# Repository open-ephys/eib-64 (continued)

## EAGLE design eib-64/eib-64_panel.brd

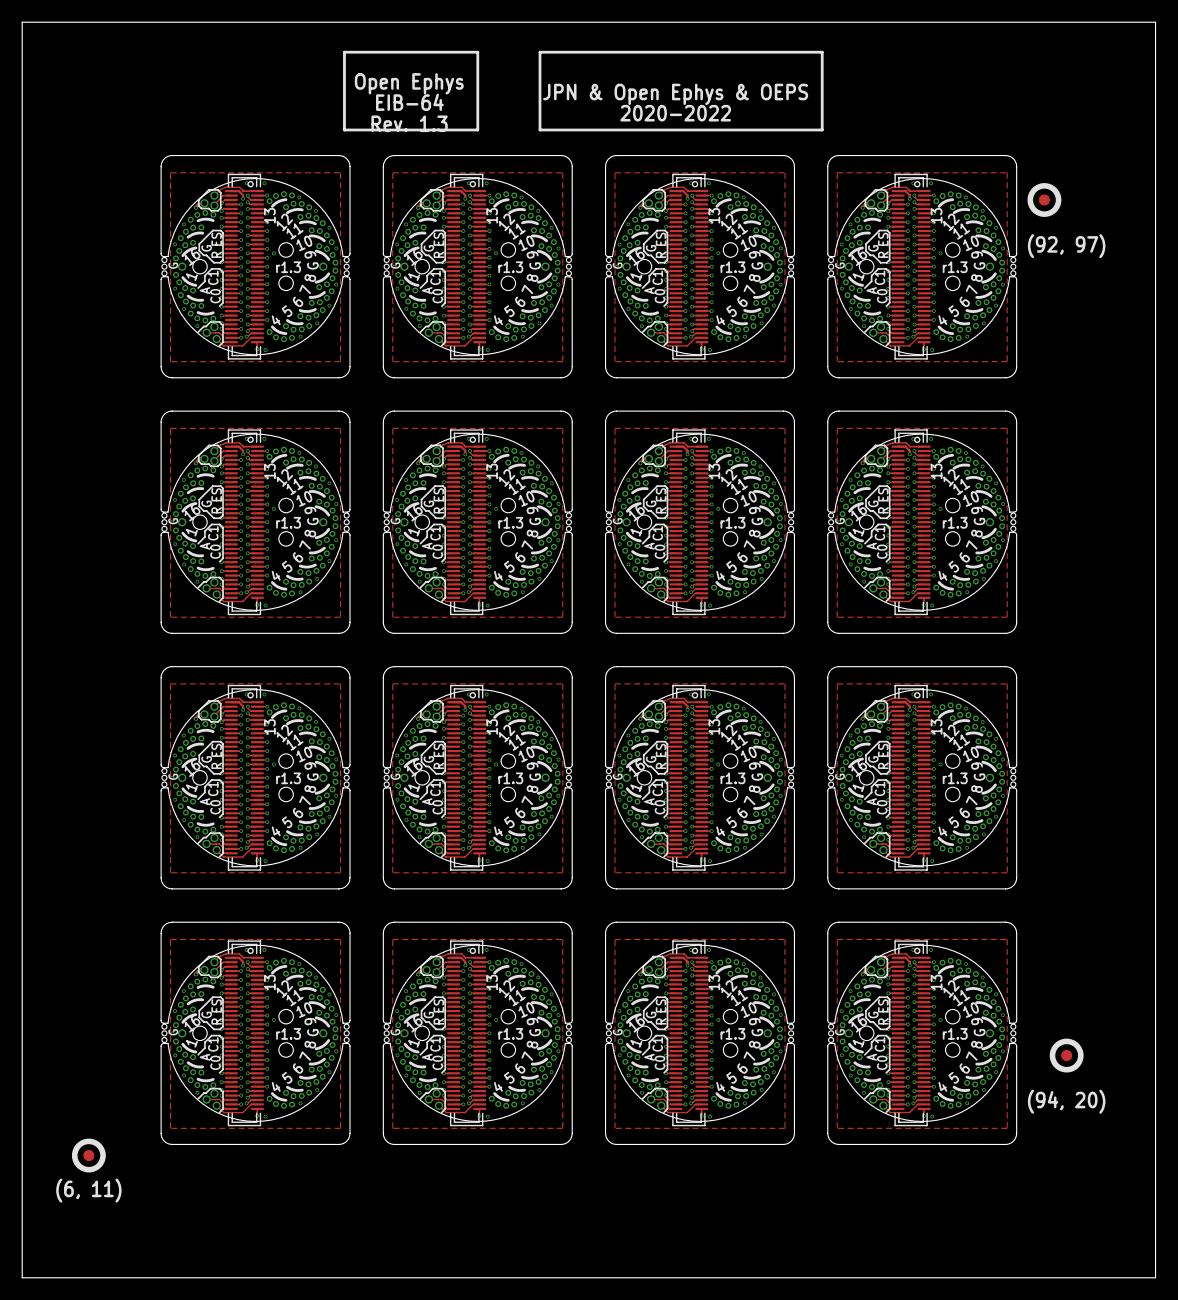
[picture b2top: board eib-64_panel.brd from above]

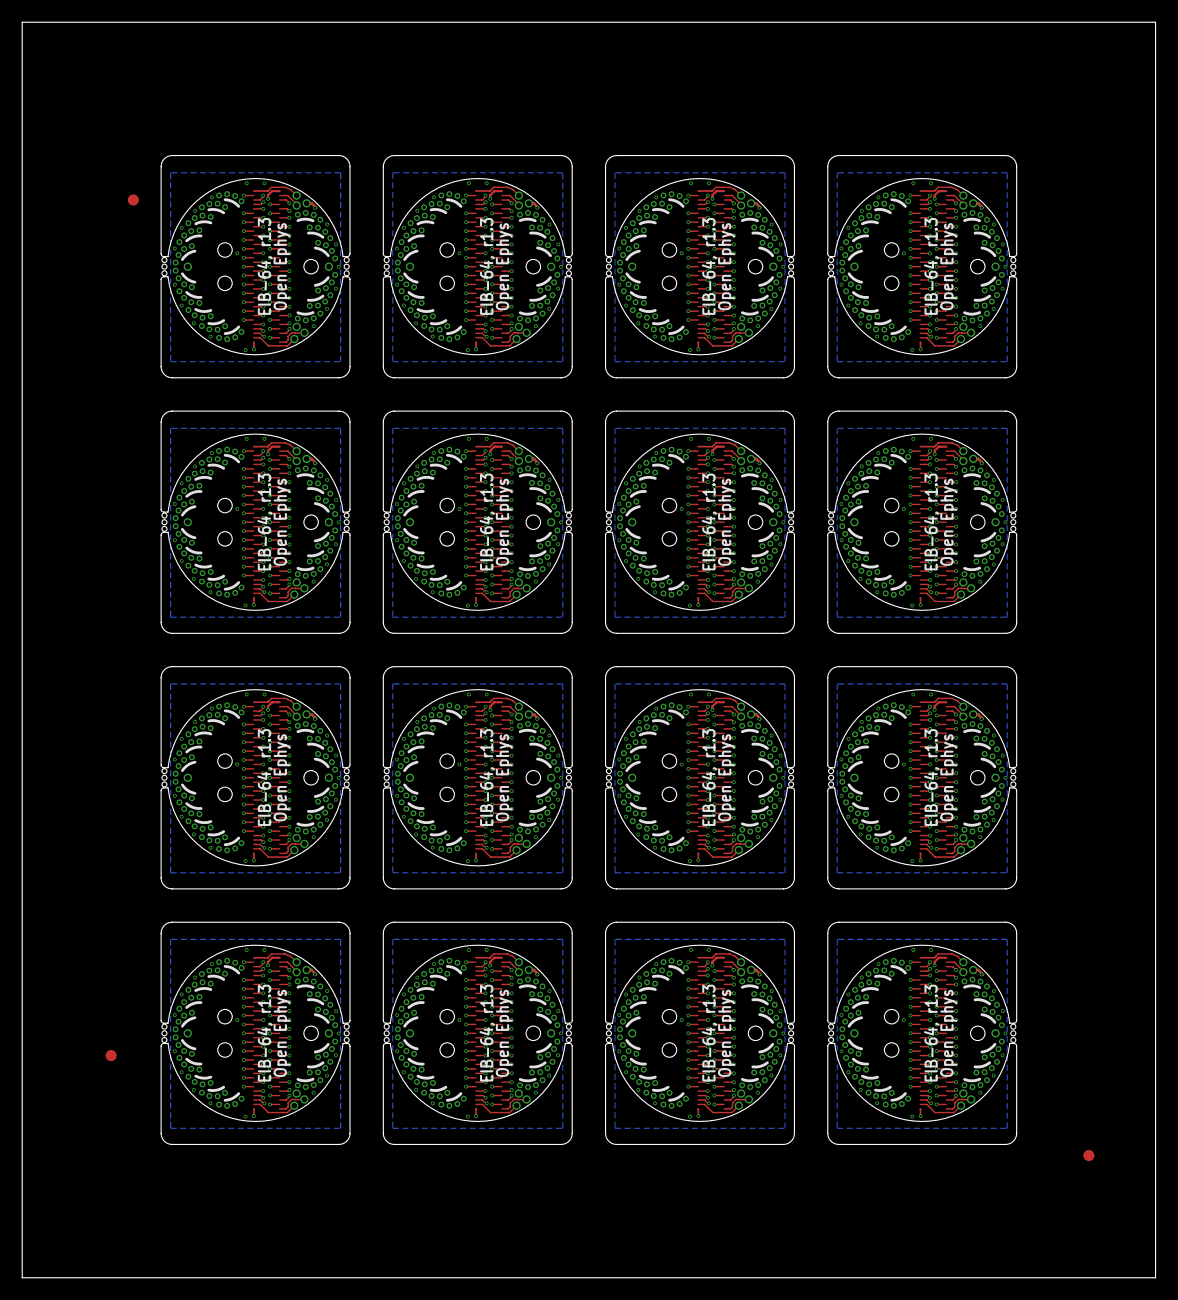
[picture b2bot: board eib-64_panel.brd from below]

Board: 4 copper layers, 102.0 x 113.0 mm, 403 parts (128 on the bottom side), 1120 nets.

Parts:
AN, AN1, AN2, AN3, AN4, AN5, AN6, AN7, AN8, AN9, AN10, AN11, AN12, AN13, AN14, AN15: LRG_GP; GOLDPIN_0.5ID_0.7OD
CAT0, CAT1, CAT2, CAT3, CAT4, CAT5, CAT6, CAT7, CAT8, CAT9, CAT10, CAT11, CAT12, CAT13, CAT14, CAT15, CAT16, CAT17, CAT18, CAT19, CAT20, CAT21, CAT22, CAT23, CAT24, CAT25, CAT26, CAT27, CAT28, CAT29, CAT30, CAT31: LRG_GP; GOLDPIN_0.5ID_0.7OD
E$1, E$2, E$4: FIDUCIAL
ESTIM, ESTIM1, ESTIM2, ESTIM3, ESTIM4, ESTIM5, ESTIM6, ESTIM7, ESTIM8, ESTIM9, ESTIM10, ESTIM11, ESTIM12, ESTIM13, ESTIM14, ESTIM15: LRG_GP; GOLDPIN_0.5ID_0.7OD
GND0, GND1, GND2, GND3, GND4, GND5, GND6, GND7, GND8, GND9, GND10, GND11, GND12, GND13, GND14, GND15, GND16, GND17, GND18, GND19, GND20, GND21, GND22, GND23, GND24, GND25, GND26, GND27, GND28, GND29, GND30, GND31: LRG_GP; GOLDPIN_0.5ID_0.7OD
J1, J2, J3, J4, J5, J6, J7, J8, J9, J10, J11, J12, J13, J14, J15, J16: DF40-REC; DF40-70REC
REF, REF1, REF2, REF3, REF4, REF5, REF6, REF7, REF8, REF9, REF10, REF11, REF12, REF13, REF14, REF15: LRG_GP; GOLDPIN_0.5ID_0.7OD
SHLD_A, SHLD_A1, SHLD_A2, SHLD_A3, SHLD_A4, SHLD_A5, SHLD_A6, SHLD_A7, SHLD_A8, SHLD_A9, SHLD_A10, SHLD_A11, SHLD_A12, SHLD_A13, SHLD_A14, SHLD_A15: LRG_GP; GOLDPIN_0.5ID_0.7OD
TET0, TET16, TET32, TET48, TET64, TET80, TET96, TET112, TET128, TET144, TET160, TET176, TET192, TET208, TET224, TET240: 0; TETRODE_0.3ID_LINEAR_MOUSE
TET1, TET17, TET33, TET49, TET65, TET81, TET97, TET113, TET129, TET145, TET161, TET177, TET193, TET209, TET225, TET241: 1; TETRODE_0.3ID_LINEAR_MOUSE
TET2, TET18, TET34, TET50, TET66, TET82, TET98, TET114, TET130, TET146, TET162, TET178, TET194, TET210, TET226, TET242: 2; TETRODE_0.3ID_LINEAR_MOUSE
TET3, TET19, TET35, TET51, TET67, TET83, TET99, TET115, TET131, TET147, TET163, TET179, TET195, TET211, TET227, TET243: 3; TETRODE_0.3ID_LINEAR_MOUSE
TET4, TET20, TET36, TET52, TET68, TET84, TET100, TET116, TET132, TET148, TET164, TET180, TET196, TET212, TET228, TET244: 4; TETRODE_0.3ID_LINEAR_MOUSE
TET5, TET21, TET37, TET53, TET69, TET85, TET101, TET117, TET133, TET149, TET165, TET181, TET197, TET213, TET229, TET245: 5; TETRODE_0.3ID_LINEAR_MOUSE
TET6, TET22, TET38, TET54, TET70, TET86, TET102, TET118, TET134, TET150, TET166, TET182, TET198, TET214, TET230, TET246: 6; TETRODE_0.3ID_LINEAR_MOUSE
TET7, TET23, TET39, TET55, TET71, TET87, TET103, TET119, TET135, TET151, TET167, TET183, TET199, TET215, TET231, TET247: 7; TETRODE_0.3ID_LINEAR_MOUSE
TET8, TET31, TET47, TET63, TET79, TET95, TET111, TET127, TET143, TET159, TET175, TET191, TET207, TET223, TET239, TET255: 8; TETRODE_0.3ID_LINEAR_MOUSE
TET9, TET30, TET46, TET62, TET78, TET94, TET110, TET126, TET142, TET158, TET174, TET190, TET206, TET222, TET238, TET254: 9; TETRODE_0.3ID_LINEAR_MOUSE
TET10, TET29, TET45, TET61, TET77, TET93, TET109, TET125, TET141, TET157, TET173, TET189, TET205, TET221, TET237, TET253: 10; TETRODE_0.3ID_LINEAR_MOUSE
TET11, TET28, TET44, TET60, TET76, TET92, TET108, TET124, TET140, TET156, TET172, TET188, TET204, TET220, TET236, TET252: 11; TETRODE_0.3ID_LINEAR_MOUSE
TET12, TET27, TET43, TET59, TET75, TET91, TET107, TET123, TET139, TET155, TET171, TET187, TET203, TET219, TET235, TET251: 12; TETRODE_0.3ID_LINEAR_MOUSE
TET13, TET26, TET42, TET58, TET74, TET90, TET106, TET122, TET138, TET154, TET170, TET186, TET202, TET218, TET234, TET250: 13; TETRODE_0.3ID_LINEAR_MOUSE
TET14, TET25, TET41, TET57, TET73, TET89, TET105, TET121, TET137, TET153, TET169, TET185, TET201, TET217, TET233, TET249: 14; TETRODE_0.3ID_LINEAR_MOUSE
TET15, TET24, TET40, TET56, TET72, TET88, TET104, TET120, TET136, TET152, TET168, TET184, TET200, TET216, TET232, TET248: 15; TETRODE_0.3ID_LINEAR_MOUSE

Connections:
AN: AN.P$1, J1.36
AN1: AN1.P$1, J2.36
AN2: AN2.P$1, J3.36
AN3: AN3.P$1, J4.36
AN4: AN4.P$1, J5.36
AN5: AN5.P$1, J6.36
AN6: AN6.P$1, J7.36
AN7: AN7.P$1, J8.36
AN8: AN8.P$1, J9.36
AN9: AN9.P$1, J10.36
AN10: AN10.P$1, J11.36
AN11: AN11.P$1, J12.36
AN12: AN12.P$1, J13.36
AN13: AN13.P$1, J14.36
AN14: AN14.P$1, J15.36
AN15: AN15.P$1, J16.36
CAT0: CAT0.P$1, J1.34
CAT1: CAT1.P$1, J1.35
CAT2: CAT2.P$1, J2.34
CAT3: CAT3.P$1, J2.35
CAT4: CAT4.P$1, J3.34
CAT5: CAT5.P$1, J3.35
CAT6: CAT6.P$1, J4.34
CAT7: CAT7.P$1, J4.35
CAT8: CAT8.P$1, J5.34
CAT9: CAT9.P$1, J5.35
CAT10: CAT10.P$1, J6.34
CAT11: CAT11.P$1, J6.35
CAT12: CAT12.P$1, J7.34
CAT13: CAT13.P$1, J7.35
CAT14: CAT14.P$1, J8.34
CAT15: CAT15.P$1, J8.35
CAT16: CAT16.P$1, J9.34
CAT17: CAT17.P$1, J9.35
CAT18: CAT18.P$1, J10.34
CAT19: CAT19.P$1, J10.35
CAT20: CAT20.P$1, J11.34
CAT21: CAT21.P$1, J11.35
CAT22: CAT22.P$1, J12.34
CAT23: CAT23.P$1, J12.35
CAT24: CAT24.P$1, J13.34
CAT25: CAT25.P$1, J13.35
CAT26: CAT26.P$1, J14.34
CAT27: CAT27.P$1, J14.35
CAT28: CAT28.P$1, J15.34
CAT29: CAT29.P$1, J15.35
CAT30: CAT30.P$1, J16.34
CAT31: CAT31.P$1, J16.35
ESTIM: ESTIM.P$1, J1.1
ESTIM1: ESTIM1.P$1, J2.1
ESTIM2: ESTIM2.P$1, J3.1
ESTIM3: ESTIM3.P$1, J4.1
ESTIM4: ESTIM4.P$1, J5.1
ESTIM5: ESTIM5.P$1, J6.1
ESTIM6: ESTIM6.P$1, J7.1
ESTIM7: ESTIM7.P$1, J8.1
ESTIM8: ESTIM8.P$1, J9.1
ESTIM9: ESTIM9.P$1, J10.1
ESTIM10: ESTIM10.P$1, J11.1
ESTIM11: ESTIM11.P$1, J12.1
ESTIM12: ESTIM12.P$1, J13.1
ESTIM13: ESTIM13.P$1, J14.1
ESTIM14: ESTIM14.P$1, J15.1
ESTIM15: ESTIM15.P$1, J16.1
GND: GND0.P$1, GND1.P$1, J1.70, SHLD_A.P$1
GND1: GND2.P$1, GND3.P$1, J2.70, SHLD_A1.P$1
GND2: GND4.P$1, GND5.P$1, J3.70, SHLD_A2.P$1
GND3: GND6.P$1, GND7.P$1, J4.70, SHLD_A3.P$1
GND4: GND8.P$1, GND9.P$1, J5.70, SHLD_A4.P$1
GND5: GND10.P$1, GND11.P$1, J6.70, SHLD_A5.P$1
GND6: GND12.P$1, GND13.P$1, J7.70, SHLD_A6.P$1
GND7: GND14.P$1, GND15.P$1, J8.70, SHLD_A7.P$1
GND8: GND16.P$1, GND17.P$1, J9.70, SHLD_A8.P$1
GND9: GND18.P$1, GND19.P$1, J10.70, SHLD_A9.P$1
GND10: GND20.P$1, GND21.P$1, J11.70, SHLD_A10.P$1
GND11: GND22.P$1, GND23.P$1, J12.70, SHLD_A11.P$1
GND12: GND24.P$1, GND25.P$1, J13.70, SHLD_A12.P$1
GND13: GND26.P$1, GND27.P$1, J14.70, SHLD_A13.P$1
GND14: GND28.P$1, GND29.P$1, J15.70, SHLD_A14.P$1
GND15: GND30.P$1, GND31.P$1, J16.70, SHLD_A15.P$1
unnamed: J1.68, TET12.3
unnamed: J1.65, TET12.2
unnamed: J1.66, TET12.1
unnamed: J1.67, TET12.0
unnamed: J1.64, TET13.0
unnamed: J1.63, TET13.1
unnamed: J1.62, TET13.2
unnamed: J1.61, TET13.3
unnamed: J1.60, TET14.0
unnamed: J1.59, TET14.1
unnamed: J1.58, TET14.2
unnamed: J1.57, TET14.3
unnamed: J1.56, TET15.0
unnamed: J1.55, TET15.1
unnamed: J1.54, TET15.2
unnamed: J1.53, TET15.3
unnamed: J1.52, TET0.3
unnamed: J1.51, TET0.2
unnamed: J1.50, TET0.1
unnamed: J1.49, TET0.0
unnamed: J1.48, TET1.3
unnamed: J1.47, TET1.2
unnamed: J1.46, TET1.1
unnamed: J1.45, TET1.0
unnamed: J1.44, TET2.3
unnamed: J1.43, TET2.2
unnamed: J1.42, TET2.1
unnamed: J1.41, TET2.0
unnamed: J1.40, TET3.0
unnamed: J1.39, TET3.3
unnamed: J1.38, TET3.2
unnamed: J1.37, TET3.1
unnamed: J1.5, TET11.3
unnamed: J1.4, TET11.2
unnamed: J1.3, TET11.1
unnamed: J1.2, TET11.0
unnamed: J2.33, TET20.0
unnamed: J2.32, TET20.1
unnamed: J2.31, TET20.2
unnamed: J2.30, TET20.3
unnamed: J2.29, TET21.0
unnamed: J2.28, TET21.1
unnamed: J2.27, TET21.2
unnamed: J2.26, TET21.3
unnamed: J2.25, TET22.0
unnamed: J2.24, TET22.1
unnamed: J2.23, TET22.2
unnamed: J2.22, TET22.3
unnamed: J2.21, TET23.0
unnamed: J2.20, TET23.1
unnamed: J2.19, TET23.2
unnamed: J2.18, TET23.3
unnamed: J2.17, TET31.3
unnamed: J2.16, TET31.2
unnamed: J2.15, TET31.1
unnamed: J2.14, TET31.0
unnamed: J2.13, TET30.3
unnamed: J2.12, TET30.2
unnamed: J2.11, TET30.1
unnamed: J2.10, TET30.0
unnamed: J2.9, TET29.3
unnamed: J2.8, TET29.2
unnamed: J2.7, TET29.1
unnamed: J2.6, TET29.0
unnamed: J2.68, TET27.3
unnamed: J2.66, TET27.1
unnamed: J2.64, TET26.0
unnamed: J2.63, TET26.1
unnamed: J2.62, TET26.2
unnamed: J2.61, TET26.3
unnamed: J2.60, TET25.0
unnamed: J2.59, TET25.1
unnamed: J2.58, TET25.2
unnamed: J2.57, TET25.3
unnamed: J2.56, TET24.0
unnamed: J2.55, TET24.1
unnamed: J2.54, TET24.2
unnamed: J2.53, TET24.3
unnamed: J2.52, TET16.3
unnamed: J2.51, TET16.2
unnamed: J2.50, TET16.1
unnamed: J2.49, TET16.0
unnamed: J2.48, TET17.3
unnamed: J2.47, TET17.2
unnamed: J2.46, TET17.1
unnamed: J2.45, TET17.0
unnamed: J2.44, TET18.3
unnamed: J2.43, TET18.2
unnamed: J2.42, TET18.1
unnamed: J2.41, TET18.0
unnamed: J2.40, TET19.0
unnamed: J2.38, TET19.2
unnamed: J2.5, TET28.3
unnamed: J2.4, TET28.2
unnamed: J2.3, TET28.1
unnamed: J2.2, TET28.0
unnamed: J2.65, TET27.2
unnamed: J2.67, TET27.0
unnamed: J2.39, TET19.3
unnamed: J2.37, TET19.1
unnamed: J3.33, TET36.0
unnamed: J3.32, TET36.1
unnamed: J3.31, TET36.2
unnamed: J3.30, TET36.3
unnamed: J3.29, TET37.0
unnamed: J3.28, TET37.1
unnamed: J3.27, TET37.2
unnamed: J3.26, TET37.3
unnamed: J3.25, TET38.0
unnamed: J3.24, TET38.1
unnamed: J3.23, TET38.2
unnamed: J3.22, TET38.3
unnamed: J3.21, TET39.0
unnamed: J3.20, TET39.1
unnamed: J3.19, TET39.2
unnamed: J3.18, TET39.3
unnamed: J3.17, TET47.3
unnamed: J3.16, TET47.2
unnamed: J3.15, TET47.1
unnamed: J3.14, TET47.0
unnamed: J3.13, TET46.3
unnamed: J3.12, TET46.2
unnamed: J3.11, TET46.1
unnamed: J3.10, TET46.0
unnamed: J3.9, TET45.3
unnamed: J3.8, TET45.2
unnamed: J3.7, TET45.1
unnamed: J3.6, TET45.0
unnamed: J3.68, TET43.3
unnamed: J3.66, TET43.1
unnamed: J3.64, TET42.0
unnamed: J3.63, TET42.1
unnamed: J3.62, TET42.2
unnamed: J3.61, TET42.3
unnamed: J3.60, TET41.0
unnamed: J3.59, TET41.1
unnamed: J3.58, TET41.2
unnamed: J3.57, TET41.3
unnamed: J3.56, TET40.0
unnamed: J3.55, TET40.1
unnamed: J3.54, TET40.2
unnamed: J3.53, TET40.3
unnamed: J3.52, TET32.3
unnamed: J3.51, TET32.2
unnamed: J3.50, TET32.1
unnamed: J3.49, TET32.0
unnamed: J3.48, TET33.3
unnamed: J3.47, TET33.2
unnamed: J3.46, TET33.1
unnamed: J3.45, TET33.0
unnamed: J3.44, TET34.3
unnamed: J3.43, TET34.2
unnamed: J3.42, TET34.1
unnamed: J3.41, TET34.0
unnamed: J3.40, TET35.0
unnamed: J3.38, TET35.2
unnamed: J3.5, TET44.3
unnamed: J3.4, TET44.2
unnamed: J3.3, TET44.1
unnamed: J3.2, TET44.0
unnamed: J3.65, TET43.2
unnamed: J3.67, TET43.0
unnamed: J3.39, TET35.3
unnamed: J3.37, TET35.1
unnamed: J4.33, TET52.0
unnamed: J4.32, TET52.1
unnamed: J4.31, TET52.2
unnamed: J4.30, TET52.3
unnamed: J4.29, TET53.0
unnamed: J4.28, TET53.1
unnamed: J4.27, TET53.2
unnamed: J4.26, TET53.3
unnamed: J4.25, TET54.0
unnamed: J4.24, TET54.1
unnamed: J4.23, TET54.2
unnamed: J4.22, TET54.3
unnamed: J4.21, TET55.0
unnamed: J4.20, TET55.1
unnamed: J4.19, TET55.2
unnamed: J4.18, TET55.3
unnamed: J4.17, TET63.3
unnamed: J4.16, TET63.2
unnamed: J4.15, TET63.1
unnamed: J4.14, TET63.0
unnamed: J4.13, TET62.3
unnamed: J4.12, TET62.2
unnamed: J4.11, TET62.1
unnamed: J4.10, TET62.0
unnamed: J4.9, TET61.3
unnamed: J4.8, TET61.2
unnamed: J4.7, TET61.1
unnamed: J4.6, TET61.0
unnamed: J4.68, TET59.3
unnamed: J4.66, TET59.1
unnamed: J4.64, TET58.0
unnamed: J4.63, TET58.1
unnamed: J4.62, TET58.2
unnamed: J4.61, TET58.3
unnamed: J1.33, TET4.0
unnamed: J1.32, TET4.1
unnamed: J1.31, TET4.2
unnamed: J1.30, TET4.3
unnamed: J1.29, TET5.0
unnamed: J1.28, TET5.1
unnamed: J1.27, TET5.2
unnamed: J1.26, TET5.3
unnamed: J1.25, TET6.0
unnamed: J1.24, TET6.1
unnamed: J1.23, TET6.2
unnamed: J1.22, TET6.3
unnamed: J1.21, TET7.0
unnamed: J1.20, TET7.1
unnamed: J1.19, TET7.2
unnamed: J1.18, TET7.3
unnamed: J1.17, TET8.3
unnamed: J1.16, TET8.2
unnamed: J1.15, TET8.1
unnamed: J1.14, TET8.0
unnamed: J1.13, TET9.3
unnamed: J1.12, TET9.2
unnamed: J1.11, TET9.1
unnamed: J1.10, TET9.0
unnamed: J1.9, TET10.3
unnamed: J1.8, TET10.2
unnamed: J1.7, TET10.1
unnamed: J1.6, TET10.0
unnamed: J4.60, TET57.0
unnamed: J4.59, TET57.1
unnamed: J4.58, TET57.2
unnamed: J4.57, TET57.3
unnamed: J4.56, TET56.0
unnamed: J4.55, TET56.1
unnamed: J4.54, TET56.2
unnamed: J4.53, TET56.3
unnamed: J4.52, TET48.3
unnamed: J4.51, TET48.2
unnamed: J4.50, TET48.1
unnamed: J4.49, TET48.0
unnamed: J4.48, TET49.3
unnamed: J4.47, TET49.2
unnamed: J4.46, TET49.1
unnamed: J4.45, TET49.0
unnamed: J4.44, TET50.3
unnamed: J4.43, TET50.2
unnamed: J4.42, TET50.1
unnamed: J4.41, TET50.0
unnamed: J4.40, TET51.0
unnamed: J4.38, TET51.2
unnamed: J4.5, TET60.3
unnamed: J4.4, TET60.2
unnamed: J4.3, TET60.1
unnamed: J4.2, TET60.0
unnamed: J4.65, TET59.2
unnamed: J4.67, TET59.0
unnamed: J4.39, TET51.3
unnamed: J4.37, TET51.1
unnamed: J5.33, TET68.0
unnamed: J5.32, TET68.1
unnamed: J5.31, TET68.2
unnamed: J5.30, TET68.3
unnamed: J5.29, TET69.0
unnamed: J5.28, TET69.1
unnamed: J5.27, TET69.2
unnamed: J5.26, TET69.3
unnamed: J5.25, TET70.0
unnamed: J5.24, TET70.1
unnamed: J5.23, TET70.2
unnamed: J5.22, TET70.3
unnamed: J5.21, TET71.0
unnamed: J5.20, TET71.1
unnamed: J5.19, TET71.2
unnamed: J5.18, TET71.3
unnamed: J5.17, TET79.3
unnamed: J5.16, TET79.2
unnamed: J5.15, TET79.1
unnamed: J5.14, TET79.0
unnamed: J5.13, TET78.3
unnamed: J5.12, TET78.2
unnamed: J5.11, TET78.1
unnamed: J5.10, TET78.0
unnamed: J5.9, TET77.3
unnamed: J5.8, TET77.2
unnamed: J5.7, TET77.1
unnamed: J5.6, TET77.0
unnamed: J5.68, TET75.3
unnamed: J5.66, TET75.1
unnamed: J5.64, TET74.0
unnamed: J5.63, TET74.1
unnamed: J5.62, TET74.2
unnamed: J5.61, TET74.3
unnamed: J5.60, TET73.0
unnamed: J5.59, TET73.1
unnamed: J5.58, TET73.2
unnamed: J5.57, TET73.3
unnamed: J5.56, TET72.0
unnamed: J5.55, TET72.1
unnamed: J5.54, TET72.2
unnamed: J5.53, TET72.3
unnamed: J5.52, TET64.3
unnamed: J5.51, TET64.2
unnamed: J5.50, TET64.1
unnamed: J5.49, TET64.0
unnamed: J5.48, TET65.3
unnamed: J5.47, TET65.2
unnamed: J5.46, TET65.1
unnamed: J5.45, TET65.0
unnamed: J5.44, TET66.3
unnamed: J5.43, TET66.2
unnamed: J5.42, TET66.1
unnamed: J5.41, TET66.0
unnamed: J5.40, TET67.0
unnamed: J5.38, TET67.2
unnamed: J5.5, TET76.3
unnamed: J5.4, TET76.2
unnamed: J5.3, TET76.1
unnamed: J5.2, TET76.0
unnamed: J5.65, TET75.2
unnamed: J5.67, TET75.0
unnamed: J5.39, TET67.3
unnamed: J5.37, TET67.1
unnamed: J6.33, TET84.0
unnamed: J6.32, TET84.1
unnamed: J6.31, TET84.2
unnamed: J6.30, TET84.3
unnamed: J6.29, TET85.0
unnamed: J6.28, TET85.1
unnamed: J6.27, TET85.2
unnamed: J6.26, TET85.3
unnamed: J6.25, TET86.0
unnamed: J6.24, TET86.1
unnamed: J6.23, TET86.2
unnamed: J6.22, TET86.3
unnamed: J6.21, TET87.0
unnamed: J6.20, TET87.1
unnamed: J6.19, TET87.2
unnamed: J6.18, TET87.3
unnamed: J6.17, TET95.3
unnamed: J6.16, TET95.2
unnamed: J6.15, TET95.1
unnamed: J6.14, TET95.0
unnamed: J6.13, TET94.3
unnamed: J6.12, TET94.2
unnamed: J6.11, TET94.1
unnamed: J6.10, TET94.0
unnamed: J6.9, TET93.3
unnamed: J6.8, TET93.2
unnamed: J6.7, TET93.1
unnamed: J6.6, TET93.0
unnamed: J6.68, TET91.3
unnamed: J6.66, TET91.1
unnamed: J6.64, TET90.0
unnamed: J6.63, TET90.1
unnamed: J6.62, TET90.2
unnamed: J6.61, TET90.3
unnamed: J6.60, TET89.0
unnamed: J6.59, TET89.1
unnamed: J6.58, TET89.2
unnamed: J6.57, TET89.3
unnamed: J6.56, TET88.0
unnamed: J6.55, TET88.1
unnamed: J6.54, TET88.2
unnamed: J6.53, TET88.3
unnamed: J6.52, TET80.3
unnamed: J6.51, TET80.2
unnamed: J6.50, TET80.1
unnamed: J6.49, TET80.0
unnamed: J6.48, TET81.3
unnamed: J6.47, TET81.2
unnamed: J6.46, TET81.1
unnamed: J6.45, TET81.0
unnamed: J6.44, TET82.3
unnamed: J6.43, TET82.2
unnamed: J6.42, TET82.1
unnamed: J6.41, TET82.0
unnamed: J6.40, TET83.0
unnamed: J6.38, TET83.2
unnamed: J6.5, TET92.3
unnamed: J6.4, TET92.2
unnamed: J6.3, TET92.1
unnamed: J6.2, TET92.0
unnamed: J6.65, TET91.2
unnamed: J6.67, TET91.0
unnamed: J6.39, TET83.3
unnamed: J6.37, TET83.1
unnamed: J7.33, TET100.0
unnamed: J7.32, TET100.1
unnamed: J7.31, TET100.2
unnamed: J7.30, TET100.3
unnamed: J7.29, TET101.0
unnamed: J7.28, TET101.1
unnamed: J7.27, TET101.2
unnamed: J7.26, TET101.3
unnamed: J7.25, TET102.0
unnamed: J7.24, TET102.1
unnamed: J7.23, TET102.2
unnamed: J7.22, TET102.3
unnamed: J7.21, TET103.0
unnamed: J7.20, TET103.1
unnamed: J7.19, TET103.2
unnamed: J7.18, TET103.3
unnamed: J7.17, TET111.3
unnamed: J7.16, TET111.2
unnamed: J7.15, TET111.1
unnamed: J7.14, TET111.0
unnamed: J7.13, TET110.3
unnamed: J7.12, TET110.2
unnamed: J7.11, TET110.1
unnamed: J7.10, TET110.0
unnamed: J7.9, TET109.3
unnamed: J7.8, TET109.2
unnamed: J7.7, TET109.1
unnamed: J7.6, TET109.0
unnamed: J7.68, TET107.3
unnamed: J7.66, TET107.1
unnamed: J7.64, TET106.0
unnamed: J7.63, TET106.1
unnamed: J7.62, TET106.2
unnamed: J7.61, TET106.3
unnamed: J7.60, TET105.0
unnamed: J7.59, TET105.1
unnamed: J7.58, TET105.2
unnamed: J7.57, TET105.3
unnamed: J7.56, TET104.0
unnamed: J7.55, TET104.1
unnamed: J7.54, TET104.2
unnamed: J7.53, TET104.3
unnamed: J7.52, TET96.3
unnamed: J7.51, TET96.2
unnamed: J7.50, TET96.1
unnamed: J7.49, TET96.0
unnamed: J7.48, TET97.3
unnamed: J7.47, TET97.2
unnamed: J7.46, TET97.1
unnamed: J7.45, TET97.0
unnamed: J7.44, TET98.3
unnamed: J7.43, TET98.2
unnamed: J7.42, TET98.1
unnamed: J7.41, TET98.0
unnamed: J7.40, TET99.0
unnamed: J7.38, TET99.2
unnamed: J7.5, TET108.3
unnamed: J7.4, TET108.2
unnamed: J7.3, TET108.1
unnamed: J7.2, TET108.0
unnamed: J7.65, TET107.2
unnamed: J7.67, TET107.0
unnamed: J7.39, TET99.3
unnamed: J7.37, TET99.1
unnamed: J8.33, TET116.0
unnamed: J8.32, TET116.1
unnamed: J8.31, TET116.2
unnamed: J8.30, TET116.3
unnamed: J8.29, TET117.0
unnamed: J8.28, TET117.1
unnamed: J8.27, TET117.2
unnamed: J8.26, TET117.3
unnamed: J8.25, TET118.0
unnamed: J8.24, TET118.1
unnamed: J8.23, TET118.2
unnamed: J8.22, TET118.3
unnamed: J8.21, TET119.0
unnamed: J8.20, TET119.1
unnamed: J8.19, TET119.2
unnamed: J8.18, TET119.3
unnamed: J8.17, TET127.3
unnamed: J8.16, TET127.2
unnamed: J8.15, TET127.1
unnamed: J8.14, TET127.0
unnamed: J8.13, TET126.3
unnamed: J8.12, TET126.2
unnamed: J8.11, TET126.1
unnamed: J8.10, TET126.0
unnamed: J8.9, TET125.3
unnamed: J8.8, TET125.2
unnamed: J8.7, TET125.1
unnamed: J8.6, TET125.0
unnamed: J8.68, TET123.3
unnamed: J8.66, TET123.1
unnamed: J8.64, TET122.0
unnamed: J8.63, TET122.1
unnamed: J8.62, TET122.2
unnamed: J8.61, TET122.3
unnamed: J8.60, TET121.0
unnamed: J8.59, TET121.1
unnamed: J8.58, TET121.2
unnamed: J8.57, TET121.3
unnamed: J8.56, TET120.0
unnamed: J8.55, TET120.1
unnamed: J8.54, TET120.2
unnamed: J8.53, TET120.3
unnamed: J8.52, TET112.3
unnamed: J8.51, TET112.2
unnamed: J8.50, TET112.1
unnamed: J8.49, TET112.0
unnamed: J8.48, TET113.3
unnamed: J8.47, TET113.2
unnamed: J8.46, TET113.1
unnamed: J8.45, TET113.0
unnamed: J8.44, TET114.3
unnamed: J8.43, TET114.2
unnamed: J8.42, TET114.1
unnamed: J8.41, TET114.0
unnamed: J8.40, TET115.0
unnamed: J8.38, TET115.2
unnamed: J8.5, TET124.3
unnamed: J8.4, TET124.2
unnamed: J8.3, TET124.1
unnamed: J8.2, TET124.0
unnamed: J8.65, TET123.2
unnamed: J8.67, TET123.0
unnamed: J8.39, TET115.3
unnamed: J8.37, TET115.1
unnamed: J9.33, TET132.0
unnamed: J9.32, TET132.1
unnamed: J9.31, TET132.2
unnamed: J9.30, TET132.3
unnamed: J9.29, TET133.0
unnamed: J9.28, TET133.1
unnamed: J9.27, TET133.2
unnamed: J9.26, TET133.3
unnamed: J9.25, TET134.0
unnamed: J9.24, TET134.1
unnamed: J9.23, TET134.2
unnamed: J9.22, TET134.3
unnamed: J9.21, TET135.0
unnamed: J9.20, TET135.1
unnamed: J9.19, TET135.2
unnamed: J9.18, TET135.3
unnamed: J9.17, TET143.3
unnamed: J9.16, TET143.2
unnamed: J9.15, TET143.1
unnamed: J9.14, TET143.0
unnamed: J9.13, TET142.3
unnamed: J9.12, TET142.2
unnamed: J9.11, TET142.1
unnamed: J9.10, TET142.0
unnamed: J9.9, TET141.3
unnamed: J9.8, TET141.2
unnamed: J9.7, TET141.1
unnamed: J9.6, TET141.0
unnamed: J9.68, TET139.3
unnamed: J9.66, TET139.1
unnamed: J9.64, TET138.0
unnamed: J9.63, TET138.1
unnamed: J9.62, TET138.2
unnamed: J9.61, TET138.3
unnamed: J9.60, TET137.0
unnamed: J9.59, TET137.1
unnamed: J9.58, TET137.2
unnamed: J9.57, TET137.3
unnamed: J9.56, TET136.0
unnamed: J9.55, TET136.1
unnamed: J9.54, TET136.2
unnamed: J9.53, TET136.3
unnamed: J9.52, TET128.3
unnamed: J9.51, TET128.2
unnamed: J9.50, TET128.1
unnamed: J9.49, TET128.0
unnamed: J9.48, TET129.3
unnamed: J9.47, TET129.2
unnamed: J9.46, TET129.1
unnamed: J9.45, TET129.0
unnamed: J9.44, TET130.3
unnamed: J9.43, TET130.2
unnamed: J9.42, TET130.1
unnamed: J9.41, TET130.0
unnamed: J9.40, TET131.0
unnamed: J9.38, TET131.2
unnamed: J9.5, TET140.3
unnamed: J9.4, TET140.2
unnamed: J9.3, TET140.1
unnamed: J9.2, TET140.0
unnamed: J9.65, TET139.2
unnamed: J9.67, TET139.0
unnamed: J9.39, TET131.3
unnamed: J9.37, TET131.1
unnamed: J10.33, TET148.0
unnamed: J10.32, TET148.1
unnamed: J10.31, TET148.2
unnamed: J10.30, TET148.3
unnamed: J10.29, TET149.0
unnamed: J10.28, TET149.1
unnamed: J10.27, TET149.2
unnamed: J10.26, TET149.3
unnamed: J10.25, TET150.0
unnamed: J10.24, TET150.1
unnamed: J10.23, TET150.2
unnamed: J10.22, TET150.3
unnamed: J10.21, TET151.0
unnamed: J10.20, TET151.1
unnamed: J10.19, TET151.2
unnamed: J10.18, TET151.3
unnamed: J10.17, TET159.3
unnamed: J10.16, TET159.2
unnamed: J10.15, TET159.1
unnamed: J10.14, TET159.0
unnamed: J10.13, TET158.3
unnamed: J10.12, TET158.2
unnamed: J10.11, TET158.1
unnamed: J10.10, TET158.0
unnamed: J10.9, TET157.3
unnamed: J10.8, TET157.2
unnamed: J10.7, TET157.1
unnamed: J10.6, TET157.0
unnamed: J10.68, TET155.3
unnamed: J10.66, TET155.1
unnamed: J10.64, TET154.0
unnamed: J10.63, TET154.1
unnamed: J10.62, TET154.2
unnamed: J10.61, TET154.3
unnamed: J10.60, TET153.0
unnamed: J10.59, TET153.1
unnamed: J10.58, TET153.2
unnamed: J10.57, TET153.3
unnamed: J10.56, TET152.0
unnamed: J10.55, TET152.1
unnamed: J10.54, TET152.2
unnamed: J10.53, TET152.3
unnamed: J10.52, TET144.3
unnamed: J10.51, TET144.2
unnamed: J10.50, TET144.1
unnamed: J10.49, TET144.0
unnamed: J10.48, TET145.3
unnamed: J10.47, TET145.2
unnamed: J10.46, TET145.1
unnamed: J10.45, TET145.0
unnamed: J10.44, TET146.3
unnamed: J10.43, TET146.2
unnamed: J10.42, TET146.1
unnamed: J10.41, TET146.0
unnamed: J10.40, TET147.0
unnamed: J10.38, TET147.2
unnamed: J10.5, TET156.3
unnamed: J10.4, TET156.2
unnamed: J10.3, TET156.1
unnamed: J10.2, TET156.0
unnamed: J10.65, TET155.2
unnamed: J10.67, TET155.0
unnamed: J10.39, TET147.3
unnamed: J10.37, TET147.1
unnamed: J11.33, TET164.0
unnamed: J11.32, TET164.1
unnamed: J11.31, TET164.2
unnamed: J11.30, TET164.3
unnamed: J11.29, TET165.0
unnamed: J11.28, TET165.1
unnamed: J11.27, TET165.2
unnamed: J11.26, TET165.3
unnamed: J11.25, TET166.0
unnamed: J11.24, TET166.1
unnamed: J11.23, TET166.2
unnamed: J11.22, TET166.3
unnamed: J11.21, TET167.0
unnamed: J11.20, TET167.1
unnamed: J11.19, TET167.2
unnamed: J11.18, TET167.3
unnamed: J11.17, TET175.3
unnamed: J11.16, TET175.2
unnamed: J11.15, TET175.1
unnamed: J11.14, TET175.0
unnamed: J11.13, TET174.3
unnamed: J11.12, TET174.2
unnamed: J11.11, TET174.1
unnamed: J11.10, TET174.0
unnamed: J11.9, TET173.3
unnamed: J11.8, TET173.2
unnamed: J11.7, TET173.1
unnamed: J11.6, TET173.0
unnamed: J11.68, TET171.3
unnamed: J11.66, TET171.1
unnamed: J11.64, TET170.0
unnamed: J11.63, TET170.1
unnamed: J11.62, TET170.2
unnamed: J11.61, TET170.3
unnamed: J11.60, TET169.0
unnamed: J11.59, TET169.1
unnamed: J11.58, TET169.2
unnamed: J11.57, TET169.3
unnamed: J11.56, TET168.0
unnamed: J11.55, TET168.1
unnamed: J11.54, TET168.2
unnamed: J11.53, TET168.3
unnamed: J11.52, TET160.3
unnamed: J11.51, TET160.2
unnamed: J11.50, TET160.1
unnamed: J11.49, TET160.0
unnamed: J11.48, TET161.3
unnamed: J11.47, TET161.2
unnamed: J11.46, TET161.1
unnamed: J11.45, TET161.0
unnamed: J11.44, TET162.3
unnamed: J11.43, TET162.2
unnamed: J11.42, TET162.1
unnamed: J11.41, TET162.0
unnamed: J11.40, TET163.0
unnamed: J11.38, TET163.2
unnamed: J11.5, TET172.3
unnamed: J11.4, TET172.2
unnamed: J11.3, TET172.1
unnamed: J11.2, TET172.0
unnamed: J11.65, TET171.2
unnamed: J11.67, TET171.0
unnamed: J11.39, TET163.3
unnamed: J11.37, TET163.1
unnamed: J12.33, TET180.0
unnamed: J12.32, TET180.1
unnamed: J12.31, TET180.2
unnamed: J12.30, TET180.3
unnamed: J12.29, TET181.0
unnamed: J12.28, TET181.1
unnamed: J12.27, TET181.2
unnamed: J12.26, TET181.3
unnamed: J12.25, TET182.0
unnamed: J12.24, TET182.1
unnamed: J12.23, TET182.2
unnamed: J12.22, TET182.3
unnamed: J12.21, TET183.0
unnamed: J12.20, TET183.1
unnamed: J12.19, TET183.2
unnamed: J12.18, TET183.3
unnamed: J12.17, TET191.3
unnamed: J12.16, TET191.2
unnamed: J12.15, TET191.1
unnamed: J12.14, TET191.0
unnamed: J12.13, TET190.3
unnamed: J12.12, TET190.2
unnamed: J12.11, TET190.1
unnamed: J12.10, TET190.0
unnamed: J12.9, TET189.3
unnamed: J12.8, TET189.2
unnamed: J12.7, TET189.1
unnamed: J12.6, TET189.0
unnamed: J12.68, TET187.3
unnamed: J12.66, TET187.1
unnamed: J12.64, TET186.0
unnamed: J12.63, TET186.1
unnamed: J12.62, TET186.2
unnamed: J12.61, TET186.3
unnamed: J12.60, TET185.0
unnamed: J12.59, TET185.1
unnamed: J12.58, TET185.2
unnamed: J12.57, TET185.3
unnamed: J12.56, TET184.0
unnamed: J12.55, TET184.1
unnamed: J12.54, TET184.2
unnamed: J12.53, TET184.3
unnamed: J12.52, TET176.3
unnamed: J12.51, TET176.2
unnamed: J12.50, TET176.1
unnamed: J12.49, TET176.0
unnamed: J12.48, TET177.3
unnamed: J12.47, TET177.2
unnamed: J12.46, TET177.1
unnamed: J12.45, TET177.0
unnamed: J12.44, TET178.3
unnamed: J12.43, TET178.2
unnamed: J12.42, TET178.1
unnamed: J12.41, TET178.0
unnamed: J12.40, TET179.0
unnamed: J12.38, TET179.2
unnamed: J12.5, TET188.3
unnamed: J12.4, TET188.2
unnamed: J12.3, TET188.1
unnamed: J12.2, TET188.0
unnamed: J12.65, TET187.2
unnamed: J12.67, TET187.0
unnamed: J12.39, TET179.3
unnamed: J12.37, TET179.1
unnamed: J13.33, TET196.0
unnamed: J13.32, TET196.1
unnamed: J13.31, TET196.2
unnamed: J13.30, TET196.3
unnamed: J13.29, TET197.0
unnamed: J13.28, TET197.1
unnamed: J13.27, TET197.2
unnamed: J13.26, TET197.3
unnamed: J13.25, TET198.0
unnamed: J13.24, TET198.1
unnamed: J13.23, TET198.2
unnamed: J13.22, TET198.3
unnamed: J13.21, TET199.0
unnamed: J13.20, TET199.1
unnamed: J13.19, TET199.2
unnamed: J13.18, TET199.3
unnamed: J13.17, TET207.3
unnamed: J13.16, TET207.2
unnamed: J13.15, TET207.1
unnamed: J13.14, TET207.0
unnamed: J13.13, TET206.3
unnamed: J13.12, TET206.2
unnamed: J13.11, TET206.1
unnamed: J13.10, TET206.0
unnamed: J13.9, TET205.3
unnamed: J13.8, TET205.2
unnamed: J13.7, TET205.1
unnamed: J13.6, TET205.0
unnamed: J13.68, TET203.3
unnamed: J13.66, TET203.1
unnamed: J13.64, TET202.0
unnamed: J13.63, TET202.1
unnamed: J13.62, TET202.2
unnamed: J13.61, TET202.3
unnamed: J13.60, TET201.0
unnamed: J13.59, TET201.1
unnamed: J13.58, TET201.2
unnamed: J13.57, TET201.3
unnamed: J13.56, TET200.0
unnamed: J13.55, TET200.1
unnamed: J13.54, TET200.2
unnamed: J13.53, TET200.3
unnamed: J13.52, TET192.3
unnamed: J13.51, TET192.2
unnamed: J13.50, TET192.1
unnamed: J13.49, TET192.0
unnamed: J13.48, TET193.3
unnamed: J13.47, TET193.2
unnamed: J13.46, TET193.1
unnamed: J13.45, TET193.0
unnamed: J13.44, TET194.3
unnamed: J13.43, TET194.2
unnamed: J13.42, TET194.1
unnamed: J13.41, TET194.0
unnamed: J13.40, TET195.0
unnamed: J13.38, TET195.2
unnamed: J13.5, TET204.3
unnamed: J13.4, TET204.2
unnamed: J13.3, TET204.1
unnamed: J13.2, TET204.0
unnamed: J13.65, TET203.2
unnamed: J13.67, TET203.0
unnamed: J13.39, TET195.3
unnamed: J13.37, TET195.1
unnamed: J14.33, TET212.0
unnamed: J14.32, TET212.1
unnamed: J14.31, TET212.2
unnamed: J14.30, TET212.3
unnamed: J14.29, TET213.0
unnamed: J14.28, TET213.1
unnamed: J14.27, TET213.2
unnamed: J14.26, TET213.3
unnamed: J14.25, TET214.0
unnamed: J14.24, TET214.1
unnamed: J14.23, TET214.2
unnamed: J14.22, TET214.3
unnamed: J14.21, TET215.0
unnamed: J14.20, TET215.1
unnamed: J14.19, TET215.2
unnamed: J14.18, TET215.3
unnamed: J14.17, TET223.3
unnamed: J14.16, TET223.2
unnamed: J14.15, TET223.1
unnamed: J14.14, TET223.0
unnamed: J14.13, TET222.3
unnamed: J14.12, TET222.2
unnamed: J14.11, TET222.1
unnamed: J14.10, TET222.0
unnamed: J14.9, TET221.3
unnamed: J14.8, TET221.2
unnamed: J14.7, TET221.1
unnamed: J14.6, TET221.0
unnamed: J14.68, TET219.3
unnamed: J14.66, TET219.1
unnamed: J14.64, TET218.0
unnamed: J14.63, TET218.1
unnamed: J14.62, TET218.2
unnamed: J14.61, TET218.3
unnamed: J14.60, TET217.0
unnamed: J14.59, TET217.1
unnamed: J14.58, TET217.2
unnamed: J14.57, TET217.3
unnamed: J14.56, TET216.0
unnamed: J14.55, TET216.1
unnamed: J14.54, TET216.2
unnamed: J14.53, TET216.3
unnamed: J14.52, TET208.3
unnamed: J14.51, TET208.2
unnamed: J14.50, TET208.1
unnamed: J14.49, TET208.0
unnamed: J14.48, TET209.3
unnamed: J14.47, TET209.2
unnamed: J14.46, TET209.1
unnamed: J14.45, TET209.0
unnamed: J14.44, TET210.3
unnamed: J14.43, TET210.2
unnamed: J14.42, TET210.1
unnamed: J14.41, TET210.0
unnamed: J14.40, TET211.0
unnamed: J14.38, TET211.2
unnamed: J14.5, TET220.3
unnamed: J14.4, TET220.2
unnamed: J14.3, TET220.1
unnamed: J14.2, TET220.0
unnamed: J14.65, TET219.2
unnamed: J14.67, TET219.0
unnamed: J14.39, TET211.3
unnamed: J14.37, TET211.1
unnamed: J15.33, TET228.0
unnamed: J15.32, TET228.1
unnamed: J15.31, TET228.2
unnamed: J15.30, TET228.3
unnamed: J15.29, TET229.0
unnamed: J15.28, TET229.1
unnamed: J15.27, TET229.2
unnamed: J15.26, TET229.3
unnamed: J15.25, TET230.0
unnamed: J15.24, TET230.1
unnamed: J15.23, TET230.2
unnamed: J15.22, TET230.3
unnamed: J15.21, TET231.0
unnamed: J15.20, TET231.1
unnamed: J15.19, TET231.2
unnamed: J15.18, TET231.3
unnamed: J15.17, TET239.3
unnamed: J15.16, TET239.2
unnamed: J15.15, TET239.1
unnamed: J15.14, TET239.0
unnamed: J15.13, TET238.3
unnamed: J15.12, TET238.2
unnamed: J15.11, TET238.1
unnamed: J15.10, TET238.0
unnamed: J15.9, TET237.3
unnamed: J15.8, TET237.2
unnamed: J15.7, TET237.1
unnamed: J15.6, TET237.0
unnamed: J15.68, TET235.3
unnamed: J15.66, TET235.1
unnamed: J15.64, TET234.0
unnamed: J15.63, TET234.1
unnamed: J15.62, TET234.2
unnamed: J15.61, TET234.3
unnamed: J15.60, TET233.0
unnamed: J15.59, TET233.1
unnamed: J15.58, TET233.2
unnamed: J15.57, TET233.3
unnamed: J15.56, TET232.0
unnamed: J15.55, TET232.1
unnamed: J15.54, TET232.2
unnamed: J15.53, TET232.3
unnamed: J15.52, TET224.3
unnamed: J15.51, TET224.2
unnamed: J15.50, TET224.1
unnamed: J15.49, TET224.0
unnamed: J15.48, TET225.3
unnamed: J15.47, TET225.2
unnamed: J15.46, TET225.1
unnamed: J15.45, TET225.0
unnamed: J15.44, TET226.3
unnamed: J15.43, TET226.2
unnamed: J15.42, TET226.1
unnamed: J15.41, TET226.0
unnamed: J15.40, TET227.0
unnamed: J15.38, TET227.2
unnamed: J15.5, TET236.3
unnamed: J15.4, TET236.2
unnamed: J15.3, TET236.1
unnamed: J15.2, TET236.0
unnamed: J15.65, TET235.2
unnamed: J15.67, TET235.0
unnamed: J15.39, TET227.3
unnamed: J15.37, TET227.1
unnamed: J16.33, TET244.0
unnamed: J16.32, TET244.1
unnamed: J16.31, TET244.2
unnamed: J16.30, TET244.3
unnamed: J16.29, TET245.0
unnamed: J16.28, TET245.1
unnamed: J16.27, TET245.2
unnamed: J16.26, TET245.3
unnamed: J16.25, TET246.0
unnamed: J16.24, TET246.1
unnamed: J16.23, TET246.2
unnamed: J16.22, TET246.3
unnamed: J16.21, TET247.0
unnamed: J16.20, TET247.1
unnamed: J16.19, TET247.2
unnamed: J16.18, TET247.3
unnamed: J16.17, TET255.3
unnamed: J16.16, TET255.2
unnamed: J16.15, TET255.1
unnamed: J16.14, TET255.0
unnamed: J16.13, TET254.3
unnamed: J16.12, TET254.2
unnamed: J16.11, TET254.1
unnamed: J16.10, TET254.0
unnamed: J16.9, TET253.3
unnamed: J16.8, TET253.2
unnamed: J16.7, TET253.1
unnamed: J16.6, TET253.0
unnamed: J16.68, TET251.3
unnamed: J16.66, TET251.1
unnamed: J16.64, TET250.0
unnamed: J16.63, TET250.1
unnamed: J16.62, TET250.2
unnamed: J16.61, TET250.3
unnamed: J16.60, TET249.0
unnamed: J16.59, TET249.1
unnamed: J16.58, TET249.2
unnamed: J16.57, TET249.3
unnamed: J16.56, TET248.0
unnamed: J16.55, TET248.1
unnamed: J16.54, TET248.2
unnamed: J16.53, TET248.3
unnamed: J16.52, TET240.3
unnamed: J16.51, TET240.2
unnamed: J16.50, TET240.1
unnamed: J16.49, TET240.0
unnamed: J16.48, TET241.3
unnamed: J16.47, TET241.2
unnamed: J16.46, TET241.1
unnamed: J16.45, TET241.0
unnamed: J16.44, TET242.3
unnamed: J16.43, TET242.2
unnamed: J16.42, TET242.1
unnamed: J16.41, TET242.0
unnamed: J16.40, TET243.0
unnamed: J16.38, TET243.2
unnamed: J16.5, TET252.3
unnamed: J16.4, TET252.2
unnamed: J16.3, TET252.1
unnamed: J16.2, TET252.0
unnamed: J16.65, TET251.2
unnamed: J16.67, TET251.0
unnamed: J16.39, TET243.3
unnamed: J16.37, TET243.1
REF: J1.69, REF.P$1
REF1: J2.69, REF1.P$1
REF2: J3.69, REF2.P$1
REF3: J4.69, REF3.P$1
REF4: J5.69, REF4.P$1
REF5: J6.69, REF5.P$1
REF6: J7.69, REF6.P$1
REF7: J8.69, REF7.P$1
REF8: J9.69, REF8.P$1
REF9: J10.69, REF9.P$1
REF10: J11.69, REF10.P$1
REF11: J12.69, REF11.P$1
REF12: J13.69, REF12.P$1
REF13: J14.69, REF13.P$1
REF14: J15.69, REF14.P$1
REF15: J16.69, REF15.P$1

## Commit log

2017-11-18 Created eib-64
    - Fits headstage-64
    - Also, put a keepout layer in eib-128 and eib-256 around the edge where
    the PCB makes contact with the drive body
2017-12-03 Fixed missing 1.8v power intput to serializer in headstage-64
    - Added values to components missing them
    - Completed ERC and DRC
    - Should be ready for fab pending final checks by other ppl
2017-12-23 Getting documentation and licensing in order
    - All subdirectories need to have their own README and license
    - This commit starts doing that
2017-12-24 More README updates
    - READMEs for the nanoz adapters
    - Links provided in top level README
2017-12-29 oepcie Specification.md update
    - Text before actual API is pretty much up to date with the latest
    firmware
    - Small changes to some READMEs
2018-03-12 Minor improvements to headstage-256 routing
    - Also remove all eagle.epf files because they are useless
2018-04-05 Reduced size of eib-64
    - Also created v-cut panelized board with 12 eibs
2018-04-15 Lots of small fixes and cleanup
    - Taking care of little issues that have been bothering me
    - Dediated serdes interface board moved to deprecated
    - Non-serialized headstage moved to deprecated
    - Deleted top-level datasheets directory which does not really
    apply to anything anymore
    - Added pdfs versions of board schematics so that eagle is not
2018-04-15 More cleanup
    - Add stencil gerbers for all eibs and eib panels
    - Remove unused intermediate design files
2018-04-19 Updated eib-64 to meet seeed low-cost spec
    - 8 mil trace/pour spacing
    - Added stencil gerbers as well
2018-08-27 eib-64 rev. 1.1
    - Fits latest shuttle drive reatining feature.
2018-10-14 Github site update
    - Bring READMEs up to date, more or less
    - Files for local Jekyll build
    - All pdfs, images, etc moved to LFS
2018-10-14 Restore images and spec.pdf from lfs
    - These files are used by the website and github pages does not support
    git lfs
2019-03-05 Increased size of eib-64 panel
    - To fit minimal requirement of 7cm x 7cm for JLCPCB
2019-07-28 Updates to eib-64 for latest shuttle drives
    - Decreased outer diameter
    - Removed flat spots because they are not required anymore (headstage
    retention clips were removed from drive body design)
    - Remade panel and added labelled fiducial marks as per Filipe's
    requirments
2019-07-29 Address Filipe's issues with eib-64 prior to fabrication
    - Move mouse bites on panel away from connector since it will be hard to
    sand under there.
    - Reduce ground planes around mouse bites to prvent exposued copper
    after sanding.
    - Adde "Open Ephys" to bottom silk.
2019-11-25 Update EIBs and add eib-64-large
    - eib-64-large is identical to eib-64, except that it fits large shuttle
    drives. It is intended as stand in for early adopters who work with rats
    and want to use the large shuttle drive
    - Update READMEs of other EIBs
2020-02-06 headstage-64 rev. 1.4 along with all dependencies
    - This is headstage-64 revision 1.4. Because it involves a change in the
    bottom analog connector, a lot of other boards had to be changed to
    match the new pinout. That is why there are so many files in this
    commit. Changes in revision 1.4 and affects on other boards are as
    follows:
    1. The coaxial adapter board has been improved to allow a regulator to
2020-05-27 Added pinout documentation for eib-64
2020-06-08 Added frozen eib-64/revisions/rev-1.2
    - This is the beta-test revision of the eib
2020-08-28 Move entire repository to CC BY-NC-SA 4.0
2021-08-30 Moved eib-64 into a dedicated repository
    - Also, did some cleanup and got rid of lfs
2021-08-30 Update README.md
    - Remove pinout from main README
2021-08-30 Update README.md
    - Fix incorrect figure in
2021-09-01 Add license
    - CC BY-NC-SA 4.0
2022-12-29 Updated the layout with an extra hole for a fiber.
2022-12-29 Updated the panel with the new layout.
2022-12-29 Updated gerber files.
2022-12-29 Added centroids for assembly.
2023-01-23 Update README.md
    Added link to google spreadsheet with channel map
2024-03-20 Corrected schematic PDF file.
